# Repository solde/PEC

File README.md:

# Smart Chicken
## PEC 2018-2019 Q1

> By Pau Serra & David Soldevila

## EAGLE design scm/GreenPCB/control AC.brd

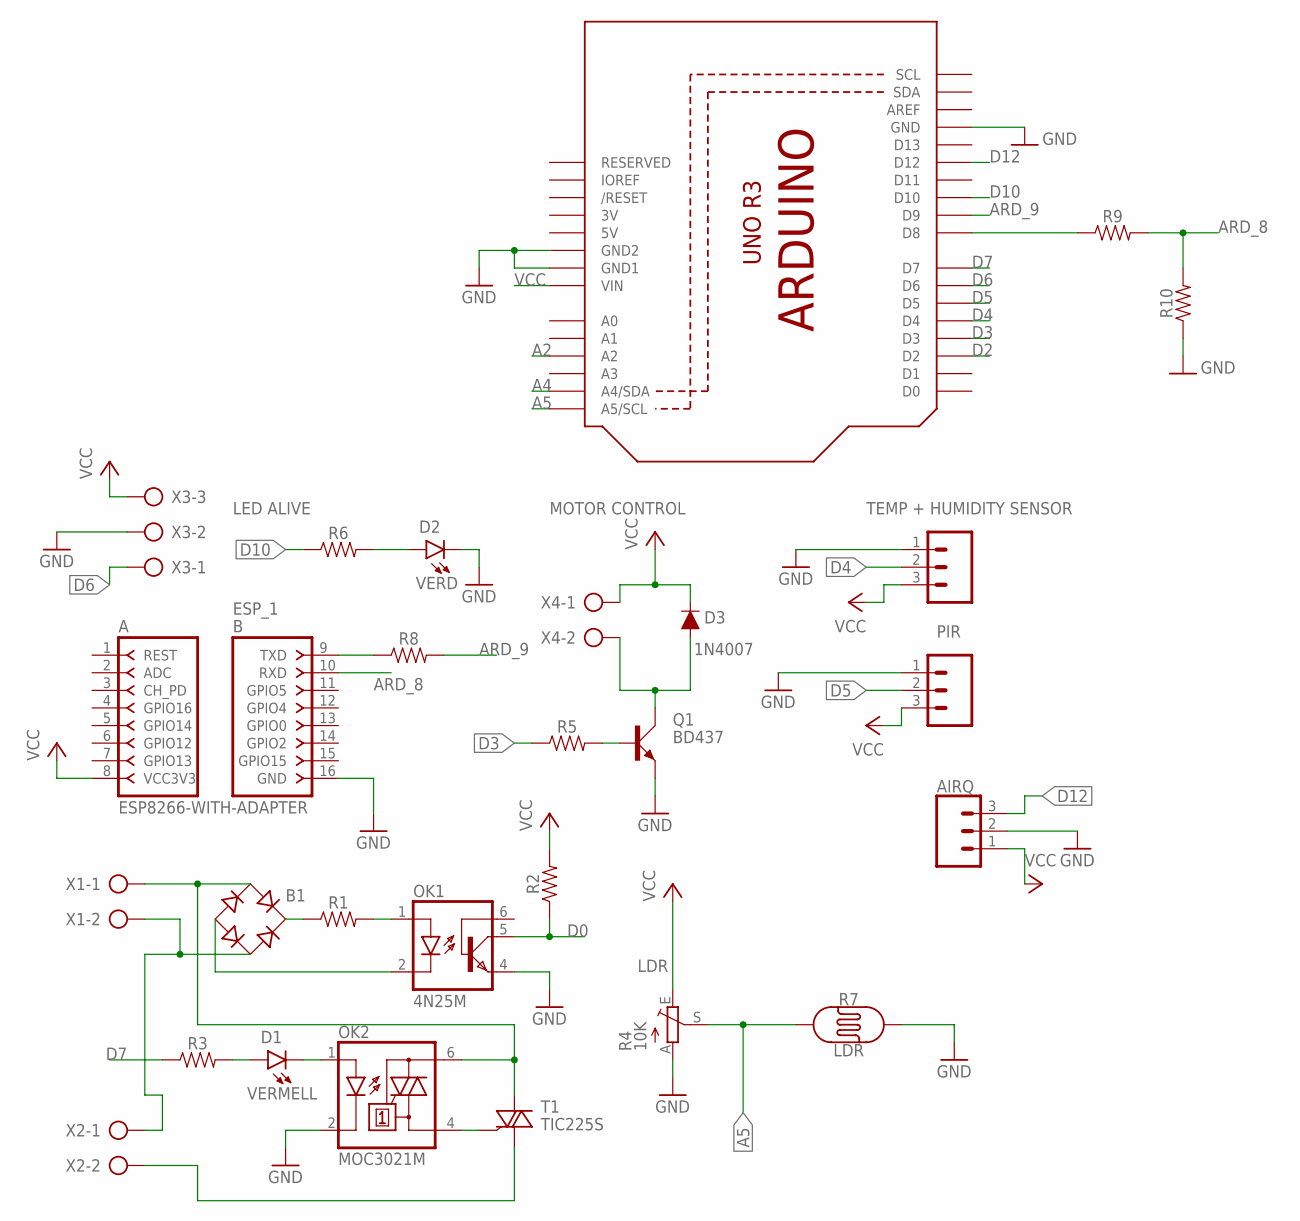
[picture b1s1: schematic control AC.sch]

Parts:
AIRQ: CONN_03; 1X03
B1: RB1A
D1: VERMELL; LED-1206
D2: VERD; FKIT-LED-1206
D3: 1N4007; DIODE-1N4001
ESP_1: ESP8266-WITH-ADAPTER; ESP8266-ADAPTER
OK1: 4N25M; DIL06
OK2: MOC3021M; DIL06
PIR: 455-1750-1-ND; 1X03
Q1: BD437; TO126AV
R1, R2, R3, R5, R6, R8, R9, R10: 0805
R4: 10K; LI10
R7: LDR; PHOTOCELL-KIT
T1: TIC225S; TO220DS
TEMP+HUM: 455-1750-1-ND; 1X03
U2: ARDUINOR3-DIMENSION; ARDUINOR3
X1, X2, X4: AK500/2
X3: AK500/3

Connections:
3V: U2.3V
5V: U2.5V
A2: U2.A2
A4: U2.A4 (A4/SDA)
A5: R4.S, R7.1, U2.A5 (A5/SCL)
ARD_8: ESP_1.10 (RXD), R9.2, R10.2
ARD_9: R8.2, U2.D9
D0: OK1.5 (COL), R2.1
D2: U2.D2
D3: R5.1, U2.D3
D4: TEMP+HUM.2, U2.D4
D5: PIR.2, U2.D5
D6: U2.D6, X3.1
D7: R3.1, U2.D7
D10: R6.1, U2.D10
D12: AIRQ.3, U2.D12
GND: AIRQ.2, D2.C, ESP_1.16 (GND), OK1.4 (EMI), OK2.2 (C), PIR.1, Q1.E, R4.A, R7.2, R10.1, TEMP+HUM.1, U2.GND, U2.GND1, U2.GND2, X3.2
unnamed: OK1.1 (A), R1.2
unnamed: B1.+, R1.1
unnamed: B1.-, OK1.2 (C)
unnamed: B1.AC1, OK2.6 (A2), T1.A2, X1.1
unnamed: B1.AC2, X1.2, X2.1
unnamed: Q1.B, R5.2
unnamed: D1.A, R3.2
unnamed: D1.C, OK2.1 (A)
unnamed: D2.A, R6.2
unnamed: OK2.4 (A1), T1.G
unnamed: T1.A1, X2.2
unnamed: D3.A, Q1.C, X4.2
unnamed: ESP_1.9 (TXD), R8.1
unnamed: R9.1, U2.D8
VCC: AIRQ.1, D3.C, ESP_1.8 (VCC3V3), PIR.3, R2.2, R4.E, TEMP+HUM.3, U2.VIN, X3.3, X4.1

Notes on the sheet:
LED ALIVE
MOTOR CONTROL
TEMP + HUMIDITY SENSOR
PIR
LDR

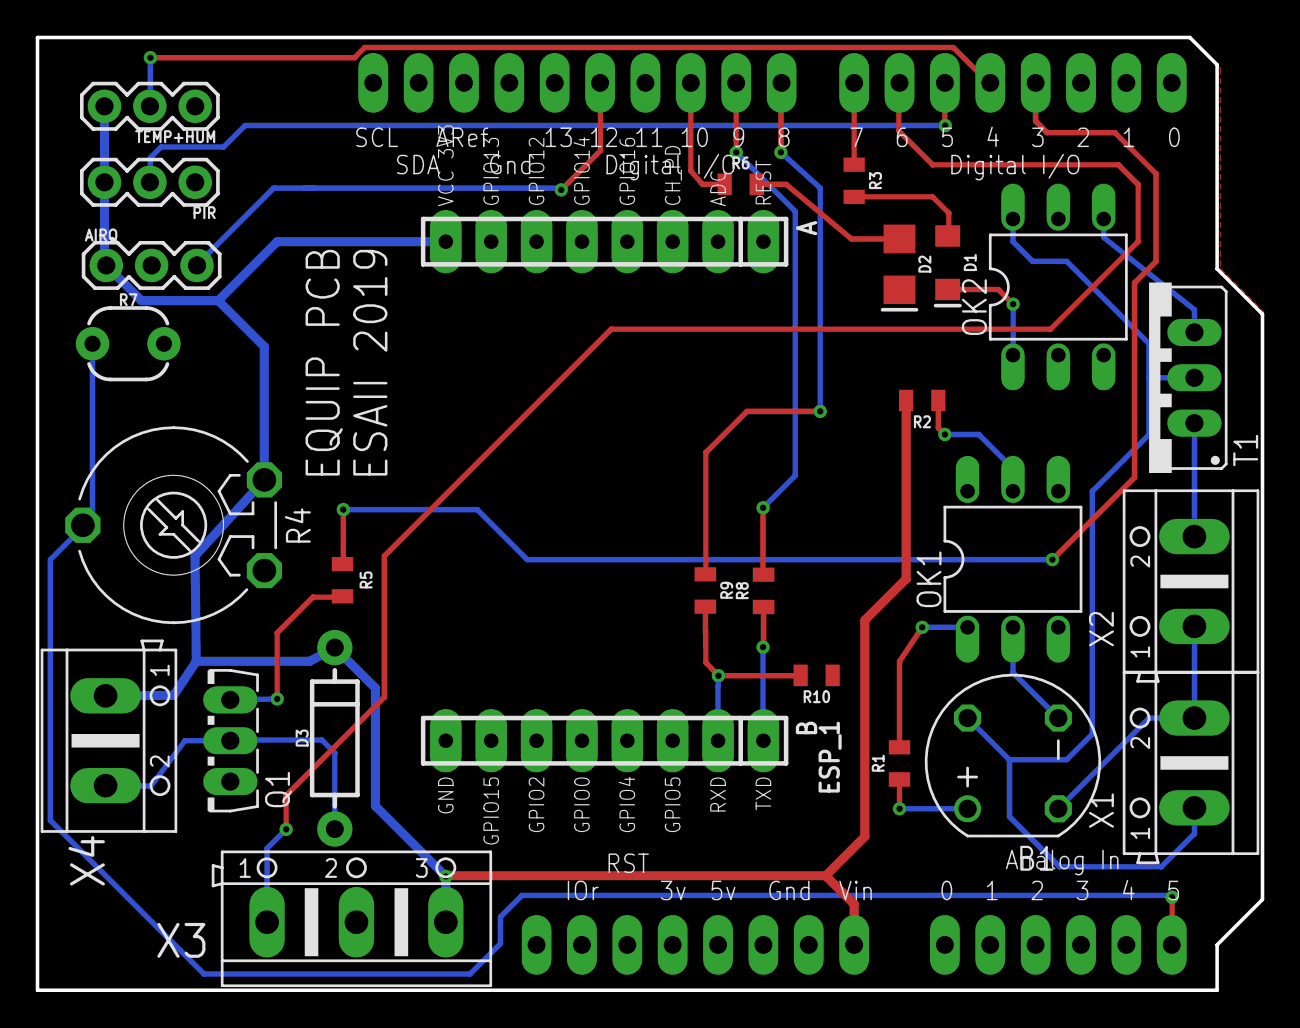
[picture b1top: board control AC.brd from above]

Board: 2 copper layers, 68.6 x 53.3 mm, 27 parts (0 on the bottom side), 27 nets.

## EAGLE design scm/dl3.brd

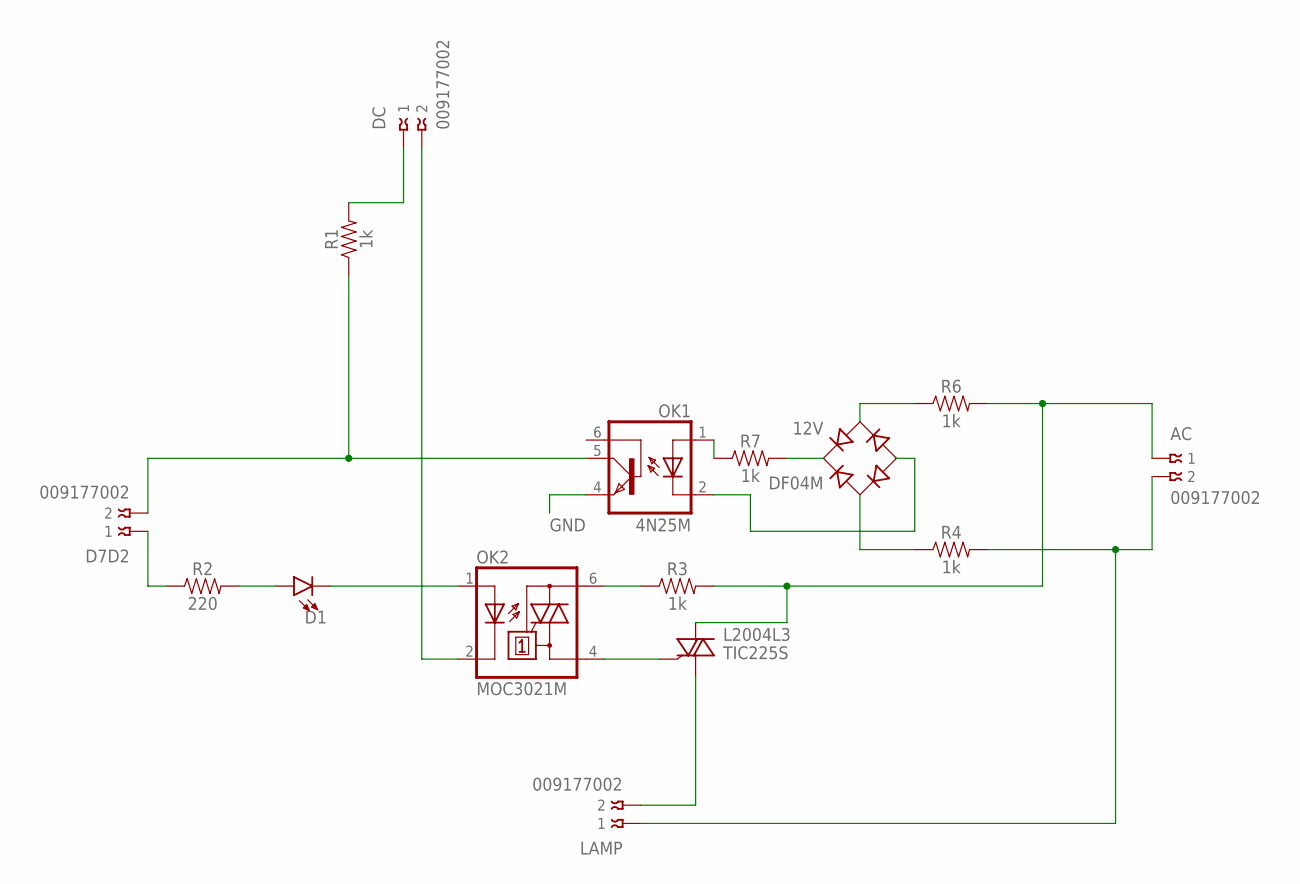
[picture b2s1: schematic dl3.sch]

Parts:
AC: 009177002
D1: LED1206; LED-1206
D7D2: 009177002
DC: 009177002
DF04M: 12V; B-DIL
L2004L3: TIC225S; TO220DS
LAMP: 009177002
OK1: 4N25M; DIL06
OK2: MOC3021M; DIL06
R1, R3, R4, R6: 1k; AXIAL-0.3
R2: 220; 0805
R7: 1k; 0805

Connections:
GND: AC.2, LAMP.1, OK1.4 (EMI), R4.P$2 (2)
IO2: D7D2.2, OK1.5 (COL), R1.P$1 (1)
unnamed: DF04M.+, R7.2
unnamed: D1.A, R2.2
unnamed: D1.C, OK2.1 (A)
unnamed: D7D2.1, R2.1
unnamed: DC.1, R1.P$2 (2)
unnamed: OK2.6 (A2), R3.P$1 (1)
unnamed: L2004L3.G, OK2.4 (A1)
unnamed: OK1.1 (A), R7.1
unnamed: DF04M.-, OK1.2 (C)
unnamed: DF04M.AC1, R4.P$1 (1)
unnamed: DC.2, OK2.2 (C)
unnamed: AC.1, L2004L3.A2, R3.P$2 (2), R6.P$2 (2)
unnamed: DF04M.AC2, R6.P$1 (1)
unnamed: L2004L3.A1, LAMP.2

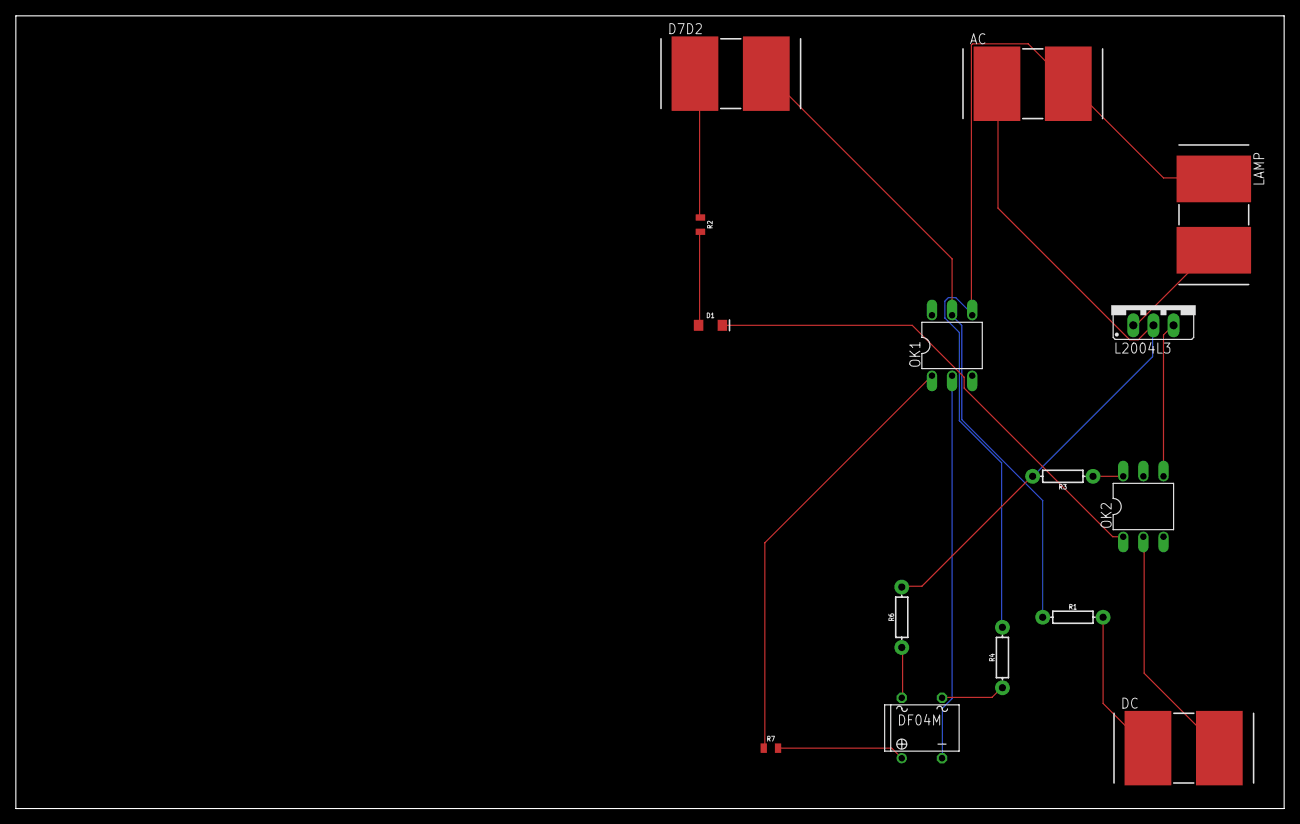
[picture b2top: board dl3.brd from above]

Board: 2 copper layers, 160.0 x 100.0 mm, 15 parts (0 on the bottom side), 16 nets.

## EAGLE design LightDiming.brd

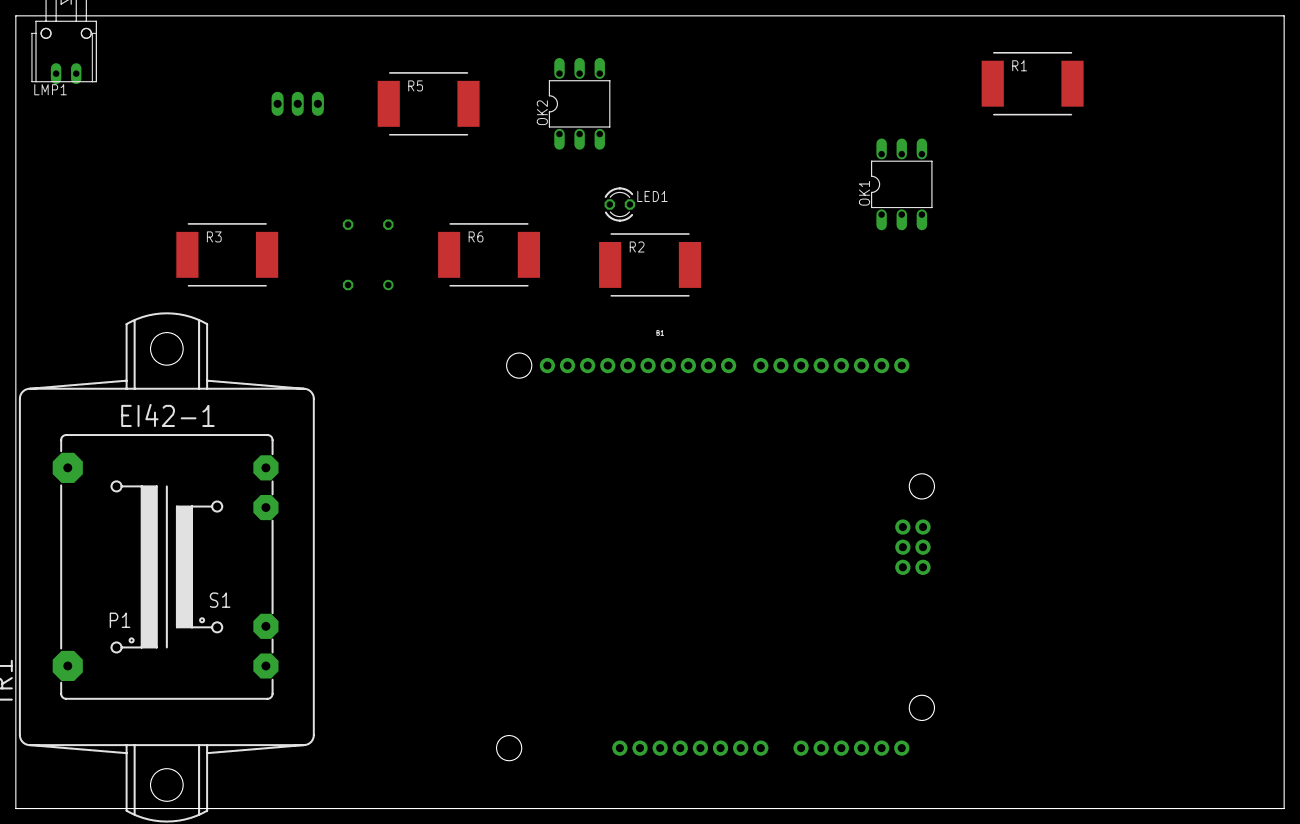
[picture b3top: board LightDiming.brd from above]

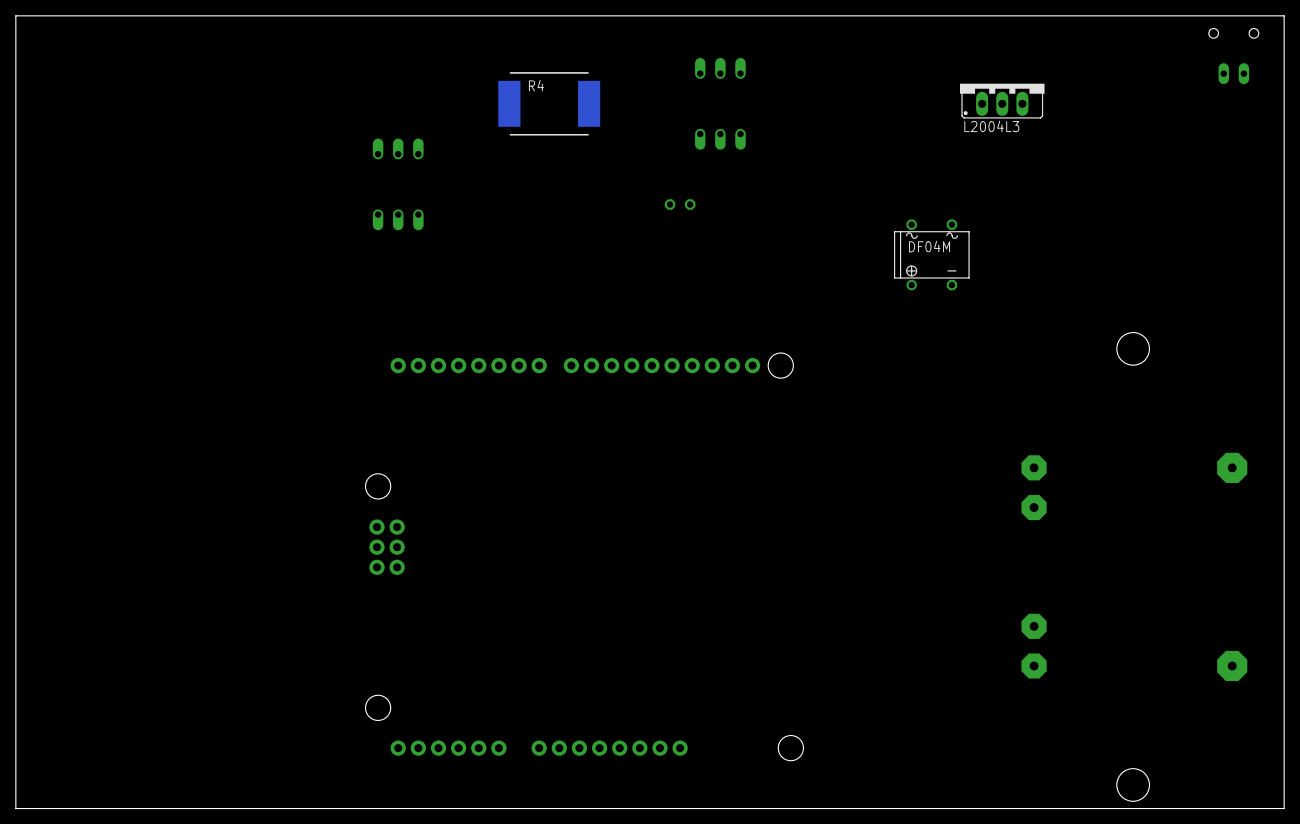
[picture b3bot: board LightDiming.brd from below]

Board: 2 copper layers, 160.0 x 100.0 mm, 14 parts (3 on the bottom side), 14 nets, no tracks yet.

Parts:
B1: ARDUINO_UNO_R3; ARDUINO_R3
DF04M: B-DIL
L2004L3: TIC225S; TO220DS
LED1: TLLR4400; LED3MM
LMP1: LDH-5R
OK1: 4N25M; DIL06
OK2: MOC3021M; DIL06
R1, R2, R3, R4, R5, R6: SMR-0
TR1: EI42-1B

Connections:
GND: LMP1.1, OK1.4, OK2.2, R4.2, TR1.7
IO0: B1.D7, R2.1
IO2: B1.D0, OK1.5, R1.2
unnamed: DF04M.+, R6.2
unnamed: LED1.A, R2.2
unnamed: LED1.K, OK2.1
unnamed: OK2.6, R5.1
unnamed: L2004L3.G, OK2.4
unnamed: OK1.1, R6.1
unnamed: DF04M.-, OK1.2
unnamed: DF04M.AC1, R4.1
unnamed: L2004L3.A2, R3.2, R5.2, TR1.9
unnamed: DF04M.AC2, R3.1
unnamed: L2004L3.A1, LMP1.2

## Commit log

2019-12-29 housing
2019-12-30 una mala soldadura es como un if mal instanciado
2019-12-30 LO IMPORTANTE ES HACER LA PCB
2020-01-02 El pico de un pato es como la cabeza de un perro
2020-01-02 dimming 2 pero idk
2020-01-16 El bec del anec es un gos
2020-01-16 Gandhi era un bon home

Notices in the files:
parts and their libraries:
SparkFun-Boards: Licensing: Creative Commons ShareAlike 4.0 International - https://creativecommons.org/licenses/by-sa/4.0
